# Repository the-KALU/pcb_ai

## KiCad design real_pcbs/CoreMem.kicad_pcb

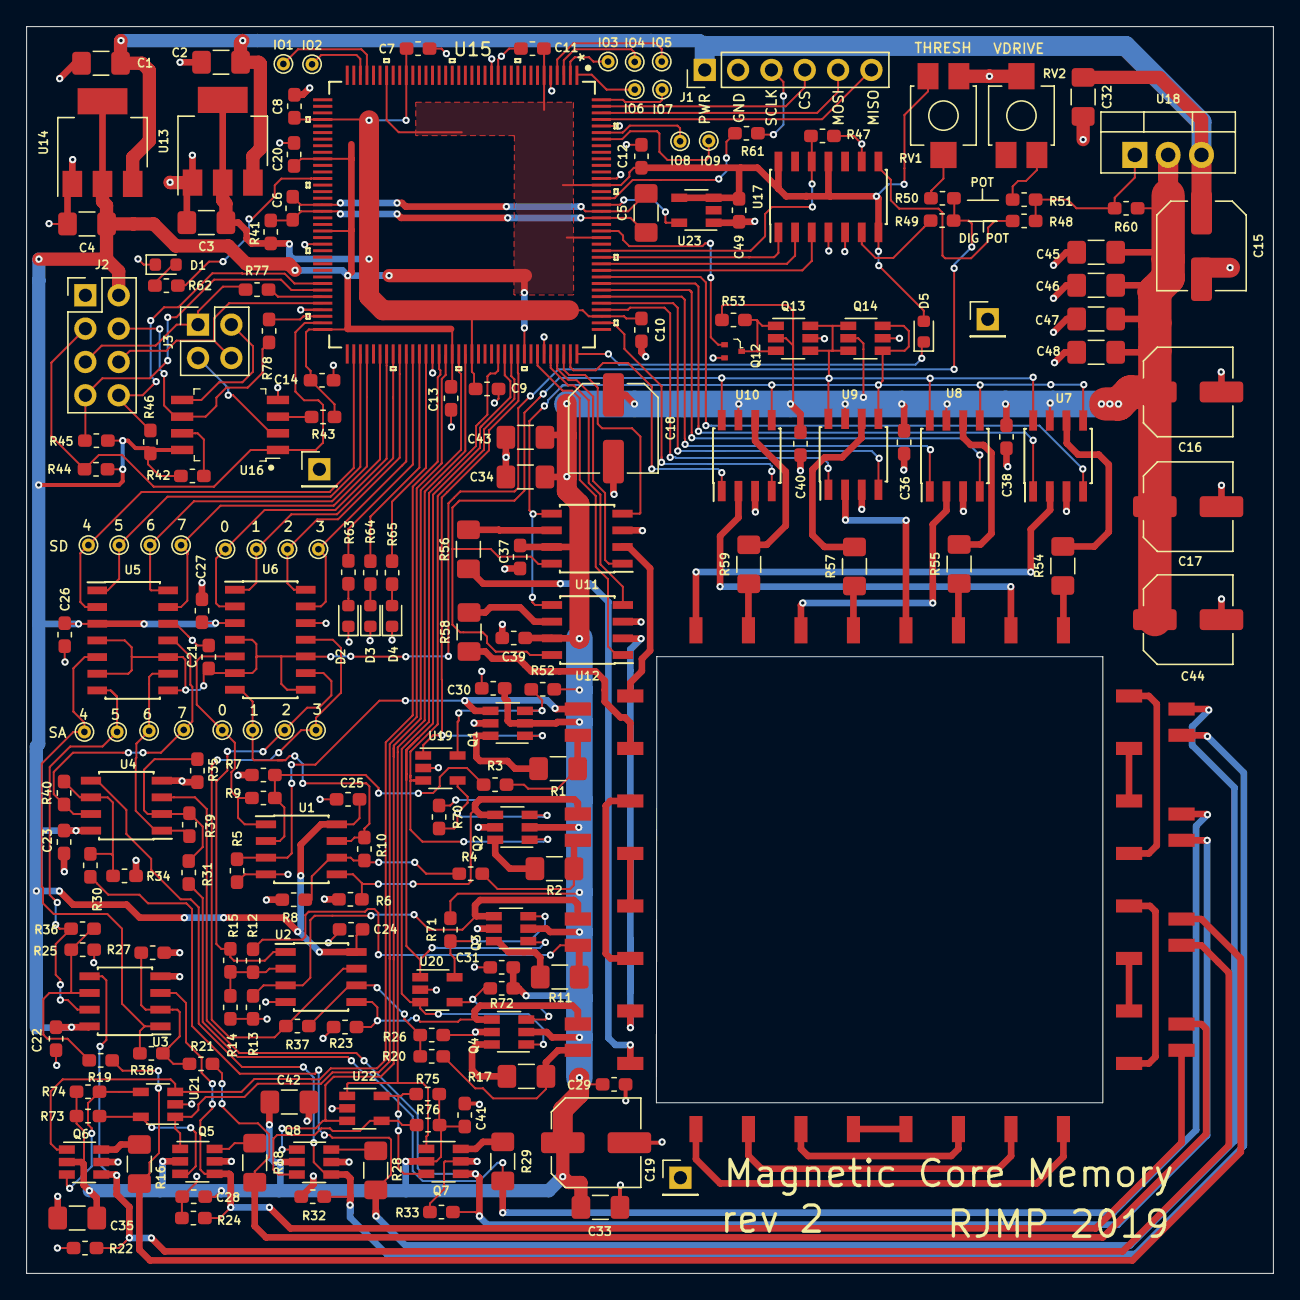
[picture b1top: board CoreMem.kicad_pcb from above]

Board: 2 copper layers, 95.0 x 95.0 mm, 196 parts (0 on the bottom side), 161 nets.

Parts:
C1, C2, C3, C4, C5, C32, C33, C34, C35, C42, C43, C45, C46, C47, C48: 10uF; C_1206_3216Metric_Pad1.42x1.75mm_HandSolder
C6, C7, C8, C9, C10, C11, C12, C13, C14, C20, C21, C22, C23, C24, C25, C26, C27, C28, C29, C30, C31, C36, C37, C38, C39, C40, C41, C49: 0.1uF; C_0603_1608Metric_Pad1.05x0.95mm_HandSolder
C15, C16, C17, C18, C19, C44: 100uF; C_Elec_6.3x7.7
D1, D2, D3, D4: LED; LED_0603_1608Metric
D5: CDBU0520; D_0603_1608Metric
F1: CoreArray
IO1, IO2, IO3, IO4, IO5, IO6, IO7, IO8, IO9: TestPoint; TestPoint_THTPad_D1.0mm_Drill0.5mm
J1: CTRL; PinHeader_1x06_P2.54mm_Vertical
J2: PROG; PinHeader_2x04_P2.54mm_Vertical
J3: Conn_02x02_Odd_Even; PinHeader_2x02_P2.54mm_Vertical
Q1, Q2, Q3, Q4, Q5, Q6, Q7, Q8, Q13, Q14: DMG6602SVTQ-7; TSOT-23-6
Q12: DMG1012T-7; SOT-523
R1, R2, R11, R16, R17, R18, R28, R29, R54, R55, R56, R57, R58, R59: 10; R_1206_3216Metric_Pad1.42x1.75mm_HandSolder
R3, R4, R12, R19, R20, R21, R30, R31: 1k; R_0603_1608Metric_Pad1.05x0.95mm_HandSolder
R5, R6, R7, R8, R9, R10, R13, R14, R15, R22, R23, R24, R25, R26, R27, R32, R33, R34, R35, R36, R37, R38, R39, R40: 22k; R_0603_1608Metric_Pad1.05x0.95mm_HandSolder
R41, R61, R77, R78: 100; R_0603_1608Metric_Pad1.05x0.95mm_HandSolder
R42, R43, R44, R45, R47, R52, R53, R60, R70, R71, R72, R73, R74, R75, R76: 10k; R_0603_1608Metric_Pad1.05x0.95mm_HandSolder
R46: 100k; R_0603_1608Metric_Pad1.05x0.95mm_HandSolder
R48, R49: 0; R_0603_1608Metric_Pad1.05x0.95mm_HandSolder
R50, R51: 0/DNP; R_0603_1608Metric_Pad1.05x0.95mm_HandSolder
R62, R63, R64, R65: 261; R_0603_1608Metric_Pad1.05x0.95mm_HandSolder
RV1, RV2: 10k; ST4EB
TP1: SA0; TestPoint_THTPad_D1.0mm_Drill0.5mm
TP2: SA1; TestPoint_THTPad_D1.0mm_Drill0.5mm
TP3: SA2; TestPoint_THTPad_D1.0mm_Drill0.5mm
TP4: SA4; TestPoint_THTPad_D1.0mm_Drill0.5mm
TP5: SA5; TestPoint_THTPad_D1.0mm_Drill0.5mm
TP6: SA3; TestPoint_THTPad_D1.0mm_Drill0.5mm
TP7: SA6; TestPoint_THTPad_D1.0mm_Drill0.5mm
TP8: SA7; TestPoint_THTPad_D1.0mm_Drill0.5mm
TP9: SD0; TestPoint_THTPad_D1.0mm_Drill0.5mm
TP10: SD1; TestPoint_THTPad_D1.0mm_Drill0.5mm
TP11: SD2; TestPoint_THTPad_D1.0mm_Drill0.5mm
TP12: SD5; TestPoint_THTPad_D1.0mm_Drill0.5mm
TP13: SD4; TestPoint_THTPad_D1.0mm_Drill0.5mm
TP14: SD3; TestPoint_THTPad_D1.0mm_Drill0.5mm
TP15: SD6; TestPoint_THTPad_D1.0mm_Drill0.5mm
TP16: SD7; TestPoint_THTPad_D1.0mm_Drill0.5mm
TP17, TP18, TP19: GND; PinHeader_1x01_P2.54mm_Vertical
U1, U2, U3, U4: OPA2365AIDR; SOIC-8_3.9x4.9mm_P1.27mm
U5, U6: TS864; SOIC-14_3.9x8.7mm_P1.27mm
U7, U8, U9, U10, U11, U12: DMHC3025LSD-13‎; SOIC-8_3.9x4.9mm_P1.27mm
U13: AZ1117-1.2; SOT-223-3_TabPin2
U14: AZ1117-3.3; SOT-223-3_TabPin2
U15: ICE40HX4K-TQ144
U16: W25Q32JVSSIQ_TR; SOIC-8_W5.6mm
U17: MCP42010; SOIC-14_3.9x8.7mm_P1.27mm
U18: LM338; TO-220-3_Vertical
U19, U20, U21, U22: QS5K2; TSOT-23-5
U23: SiT2001B; TSOT-23-5

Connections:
+1V2: C3.1, C7.1, C8.1, C9.1, C10.1, R41.2, U13.2, U15.27, U15.40, U15.92, U15.111
+3V3: C4.1, C11.1, C12.1, C13.1, C14.1, C20.1, C22.1, C23.1, C24.1, C25.1, C26.1, C27.1, C49.1, D5.2, J2.2, R42.2, R43.2, R44.2, R45.2, R46.2, RV1.1, U1.8, U2.8, U3.8, U4.8, U5.3, U6.3, U14.2, U15.6, U15.30, U15.46, U15.57, U15.72, U15.89, U15.100, U15.123, U15.131, U16.8, U17.7, U17.11, U17.14, U23.3, U23.4
/CS: J1.4, U15.143
/DIN: J1.5, U15.142
/DIR: Q12.1, U15.124
/DOUT: J1.6, U15.141
/DRIVE/DIR_F_VD: Q13.4, Q13.6, Q14.1, Q14.3, U7.8, U8.8, U9.8, U10.8, U11.8, U12.8
/DRIVE/DIR_R_VD: Q14.4, Q14.6, U7.5, U8.5, U9.5, U10.5, U11.5, U12.5
/INHIBIT0: Q1.1, U15.99, U19.1
/INHIBIT1: Q2.1, U15.98, U19.3
/INHIBIT2: Q3.1, U15.97, U20.1
/INHIBIT3: Q4.1, U15.96, U20.3
/INHIBIT4: Q5.1, U15.88, U21.1
/INHIBIT5: Q6.1, U15.87, U21.3
/INHIBIT6: Q7.1, U15.91, U22.1
/INHIBIT7: Q8.1, U15.90, U22.3
/POT_CS: U15.120, U17.1
/POT_MOSI: U15.118, U17.3
/POT_SCK: U15.119, U17.2
/POT_SHDN: R47.1, U15.121, U17.12
/S0_N: F1.34, R1.2, R3.2
/S0_P: F1.33, Q1.4, R5.2, U1.3
/S1_N: F1.36, R2.2, R4.2
/S1_P: F1.35, Q2.4, R6.2, U1.5
/S2_N: F1.38, R11.2, R12.2
/S2_P: F1.37, Q3.4, R13.2, U2.3
/S3_N: F1.40, R17.2, R20.2
/S3_P: F1.39, Q4.4, R23.2, U2.5
/S4_N: F1.47, R18.2, R21.2
/S4_P: F1.48, Q5.4, R24.2, U3.3
/S5_N: F1.45, R16.2, R19.2
/S5_P: F1.46, Q6.4, R22.2, U3.5
/S6_N: F1.43, R29.2, R31.2
/S6_P: F1.44, Q7.4, R33.2, U4.3
/S7_N: F1.41, R28.2, R30.2
/S7_P: F1.42, Q8.4, R32.2, U4.5
/SCLK: J1.3, R61.2
/SCLK_F: R61.1, U15.129
/SD0: TP9.1, U6.2, U15.79
/SD1: TP10.1, U6.1, U15.80
/SD2: TP11.1, U6.14, U15.81
/SD3: TP14.1, U6.13, U15.82
/SD4: TP13.1, U5.2, U15.74
/SD5: TP12.1, U5.1, U15.75
/SD6: TP15.1, U5.14, U15.76
/SD7: TP16.1, U5.13, U15.78
/SENSE_Conditioning/INHIBIT0n: Q1.3, R52.1, U19.5
/SENSE_Conditioning/INHIBIT1n: Q2.3, R70.2, U19.4
/SENSE_Conditioning/INHIBIT2n: Q3.3, R71.1, U20.5
/SENSE_Conditioning/INHIBIT3n: Q4.3, R72.2, U20.4
/SENSE_Conditioning/INHIBIT4n: Q5.3, R73.1, U21.5
/SENSE_Conditioning/INHIBIT5n: Q6.3, R74.1, U21.4
/SENSE_Conditioning/INHIBIT6n: Q7.3, R75.1, U22.5
/SENSE_Conditioning/INHIBIT7n: Q8.3, R76.1, U22.4
/SENSE_Conditioning/SA0: R9.2, TP1.1, U1.1, U6.5
/SENSE_Conditioning/SA1: R10.2, TP2.1, U1.7, U6.7
/SENSE_Conditioning/SA2: R15.2, TP3.1, U2.1, U6.9
/SENSE_Conditioning/SA3: R37.2, TP6.1, U2.7, U6.11
/SENSE_Conditioning/SA4: R38.2, TP4.1, U3.1, U5.5
/SENSE_Conditioning/SA5: R36.2, TP5.1, U3.7, U5.7
/SENSE_Conditioning/SA6: R39.2, TP7.1, U4.1, U5.9
/SENSE_Conditioning/SA7: R40.2, TP8.1, U4.7, U5.11
/SENSE_THRESH: C21.1, R49.1, R50.1, U5.4, U5.6, U5.8, U5.10, U6.4, U6.6, U6.8, U6.10
/VDRIVE_CONTROL: R48.1, R51.2, R60.2, U18.1
/X0_EN_F: U11.4, U15.106
/X0_EN_R: U11.1, U15.105
/X0_N: F1.8, R56.1
/X0_P: F1.1, U11.2
/X1_EN_F: U12.4, U15.104
/X1_EN_R: U12.1, U15.102
/X1_N: F1.2, R58.1
/X1_P: F1.7, U12.2
/Y0_EN_F: U7.4, U15.117
/Y0_EN_R: U7.1, U15.116
/Y0_N: F1.31, R59.1
/Y0_P: F1.32, U7.2
/Y1_EN_F: U8.4, U15.115
/Y1_EN_R: U8.1, U15.114
/Y1_N: F1.29, R57.1
/Y1_P: F1.30, U8.2
/Y2_EN_F: U9.4, U15.113
/Y2_EN_R: U9.1, U15.112
/Y2_N: F1.27, R55.1
/Y2_P: F1.28, U9.2
/Y3_EN_F: U10.4, U15.110
/Y3_EN_R: U10.1, U15.107
/Y3_N: F1.25, R54.1
/Y3_P: F1.26, U10.2
/controller/CDONE: J2.8, R46.1, U15.65
/controller/CLKIN: U15.128, U23.5
/controller/CRESET_B: J2.7, R45.1, U15.66
/controller/FLASH_DI: J3.2, U16.5
/controller/FLASH_DO: J3.3, U16.2
/controller/GNDPLL: C5.2, C6.2, U15.53, U15.127
/controller/LED0: R62.1, U15.49
/controller/LED1: R63.1, U15.83
/controller/LED2: R64.1, U15.84
/controller/LED3: R65.1, U15.85
/controller/SPI_SCK: J2.4, R78.1, U16.6
/controller/SPI_SDI: J2.6, J3.4, U15.68
/controller/SPI_SDO: J2.5, J3.1, R77.1
/controller/SPI_SS: J2.3, R44.1, U15.71, U16.1
/controller/VCCPLL: C5.1, C6.1, R41.1, U15.54, U15.126
GND: C1.2, C2.2, C3.2, C4.2, C7.2, C8.2, C9.2, C10.2, C11.2, C12.2, C13.2, C14.2, C15.2, C16.2, C17.2, C18.2, C19.2, C20.2, C21.2, C22.2, C23.2, C24.2, C25.2, C26.2, C27.2, C28.2, C29.2, C30.2, C31.2, C32.2, C33.2, C34.2, C35.2, C36.2, C37.2, C38.2, C39.2, C40.2, C41.2, C42.2, C43.2, C44.2, C45.2, C46.2, C47.2, C48.2, C49.2, D1.1, D2.1, D3.1, D4.1, J1.2, J2.1, Q1.5, Q2.5, Q3.5, Q4.5, Q5.5, Q6.5, Q7.5, Q8.5, Q12.2, Q13.5, Q14.5, R5.1, R6.1, R7.1, R8.1, R13.1, R14.1, R22.1, R23.1, R24.1, R25.1, R26.1, R27.1, R32.1, R33.1, R34.1, R35.1, R47.2, RV1.3, RV2.2, TP17.1, TP18.1, TP19.1, U1.4, U2.4, U3.4, U4.4, U5.12, U6.12, U7.3, U8.3, U9.3, U10.3, U11.3, U12.3, U13.1, U14.1, U15.5, U15.13, U15.14, U15.59, U15.69, U15.86, U15.103, U15.132, U15.140, U16.4, U17.4, U17.5, U17.9, U19.2, U20.2, U21.2, U22.2, U23.1
unnamed: D1.2, R62.2
unnamed: D2.2, R63.2
unnamed: D3.2, R64.2
unnamed: D4.2, R65.2
unnamed: D5.1, U15.108
unnamed: F1.3, F1.6
unnamed: F1.4, F1.5
unnamed: F1.10, F1.15
unnamed: F1.11, F1.14
unnamed: F1.12, F1.13
unnamed: F1.9, F1.16
unnamed: F1.17, F1.20
unnamed: F1.18, F1.19
unnamed: F1.21, F1.24
unnamed: F1.22, F1.23
unnamed: IO1.1, U15.33
unnamed: IO2.1, U15.34
unnamed: IO3.1, U15.2
unnamed: IO4.1, U15.3
unnamed: IO5.1, U15.4
unnamed: IO6.1, U15.1
unnamed: IO7.1, U15.144
unnamed: IO8.1, U15.139
unnamed: IO9.1, U15.138
unnamed: Q1.6, R1.1
unnamed: Q2.6, R2.1
unnamed: Q3.6, R11.1
unnamed: Q4.6, R17.1
unnamed: Q5.6, R18.1
unnamed: Q6.6, R16.1
unnamed: Q7.6, R29.1
unnamed: Q8.6, R28.1
unnamed: Q12.3, Q13.1, Q13.3, R53.2
unnamed: R3.1, R7.2, R9.1, U1.2
unnamed: R4.1, R8.2, R10.1, U1.6
unnamed: R12.1, R14.2, R15.1, U2.2
unnamed: R19.1, R25.2, R36.1, U3.6
unnamed: R20.1, R26.2, R37.1, U2.6
unnamed: R21.1, R27.2, R38.1, U3.2
unnamed: R30.1, R34.2, R40.1, U4.6
unnamed: R31.1, R35.2, R39.1, U4.2
unnamed: R42.1, U16.7
unnamed: R43.1, U16.3
unnamed: R48.2, U17.8
unnamed: R49.2, U17.6
unnamed: R50.2, RV1.2
unnamed: R51.1, RV2.1
unnamed: R54.2, U7.6
unnamed: R55.2, U8.6
unnamed: R56.2, U11.6
unnamed: R57.2, U9.6
unnamed: R58.2, U12.6
unnamed: R59.2, U10.6
unnamed: R77.2, U15.67
unnamed: R78.2, U15.70
VBUS: C1.1, C2.1, C15.1, C32.1, J1.1, U13.3, U14.3, U18.3
Vdrive: C16.1, C17.1, C18.1, C19.1, C28.1, C29.1, C30.1, C31.1, C33.1, C34.1, C35.1, C36.1, C37.1, C38.1, C39.1, C40.1, C41.1, C42.1, C43.1, C44.1, C45.1, C46.1, C47.1, C48.1, Q1.2, Q2.2, Q3.2, Q4.2, Q5.2, Q6.2, Q7.2, Q8.2, Q13.2, Q14.2, R52.2, R53.1, R60.1, R70.1, R71.2, R72.1, R73.2, R74.2, R75.2, R76.2, U7.7, U8.7, U9.7, U10.7, U11.7, U12.7, U18.2

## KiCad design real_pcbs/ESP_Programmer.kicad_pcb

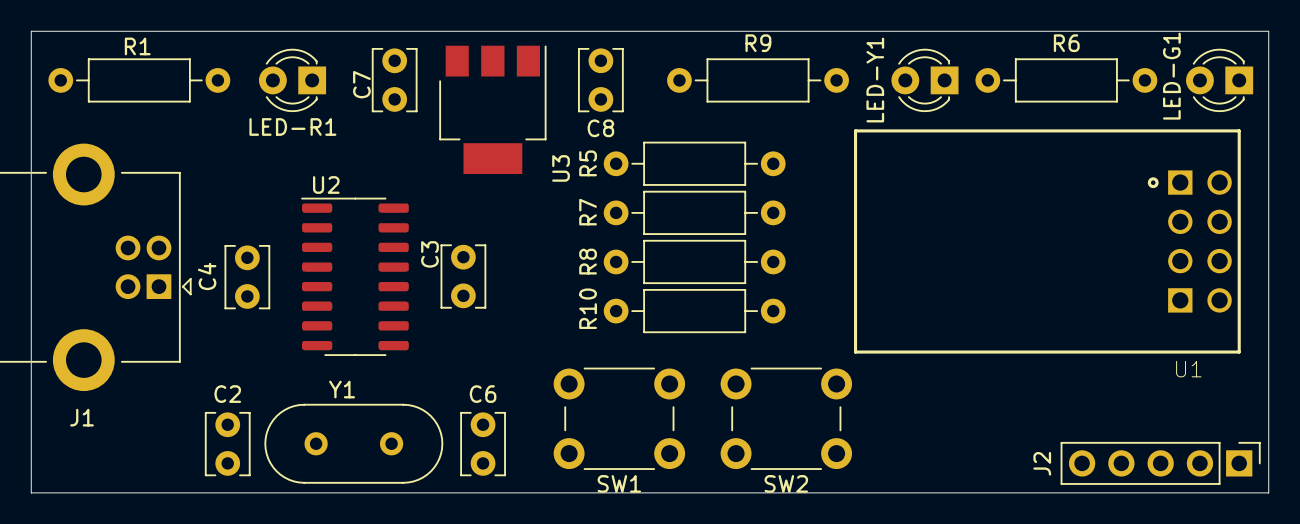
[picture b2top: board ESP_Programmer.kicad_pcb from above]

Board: 2 copper layers, 80.0 x 29.8 mm, 24 parts (0 on the bottom side), 17 nets, no tracks yet.

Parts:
C2, C6: 22pf; C_Disc_D3.8mm_W2.6mm_P2.50mm
C3: 105; C_Disc_D3.8mm_W2.6mm_P2.50mm
C4, C8: 104; C_Disc_D3.8mm_W2.6mm_P2.50mm
C7: 106; C_Disc_D3.8mm_W2.6mm_P2.50mm
J1: USB_B; USB_B_Lumberg_2411_02_Horizontal
J2: Conn_01x05_Male; PinHeader_1x05_P2.54mm_Vertical
LED-G1: LED; LED_D3.0mm_Clear
LED-R1: LED; LED_D3.0mm_Clear
LED-Y1: LED; LED_D3.0mm_Clear
R1, R6, R9: 330; R_Axial_DIN0207_L6.3mm_D2.5mm_P10.16mm_Horizontal
R5, R7, R8, R10: 10K; R_Axial_DIN0207_L6.3mm_D2.5mm_P10.16mm_Horizontal
SW1: FLASH; SW_PUSH_6mm_H4.3mm
SW2: RESET; SW_PUSH_6mm_H4.3mm
U1: ESP8266-01_ESP-01; ESP-01
U2: CH340G; SOIC-16_3.9x9.9mm_P1.27mm
U3: AMS1117; SOT-223-3_TabPin2
Y1: 12MHz; Crystal_HC49-4H_Vertical

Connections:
3.3v: C8.1, J2.3, R5.2, R7.1, R8.1, R9.1, U1.8, U3.2
+5V: C3.1, C7.1, J1.1, J2.2, R1.1, U2.16, U3.3
/CH_PD: R8.2, U1.6
/D+: J1.3, U2.5
/D-: J1.2, U2.6
/IO0: R5.1, SW1.2, U1.2
/IO2: R6.1, U1.3
/RST: R7.2, SW2.2, U1.7
ESP_RXD: J2.4, U1.1, U2.2
ESP_TXD: J2.5, R10.1, U1.5, U2.3
GND: C2.2, C3.2, C4.2, C6.2, C7.2, C8.2, J1.4, J1.5, J2.1, LED-G1.1, LED-R1.1, LED-Y1.1, R10.2, SW1.1, SW2.1, U1.4, U2.1, U3.1
unnamed: C2.1, U2.7, Y1.1
unnamed: C4.1, U2.4
unnamed: C6.1, U2.8, Y1.2
unnamed: LED-G1.2, R6.2
unnamed: LED-R1.2, R1.2
unnamed: LED-Y1.2, R9.2

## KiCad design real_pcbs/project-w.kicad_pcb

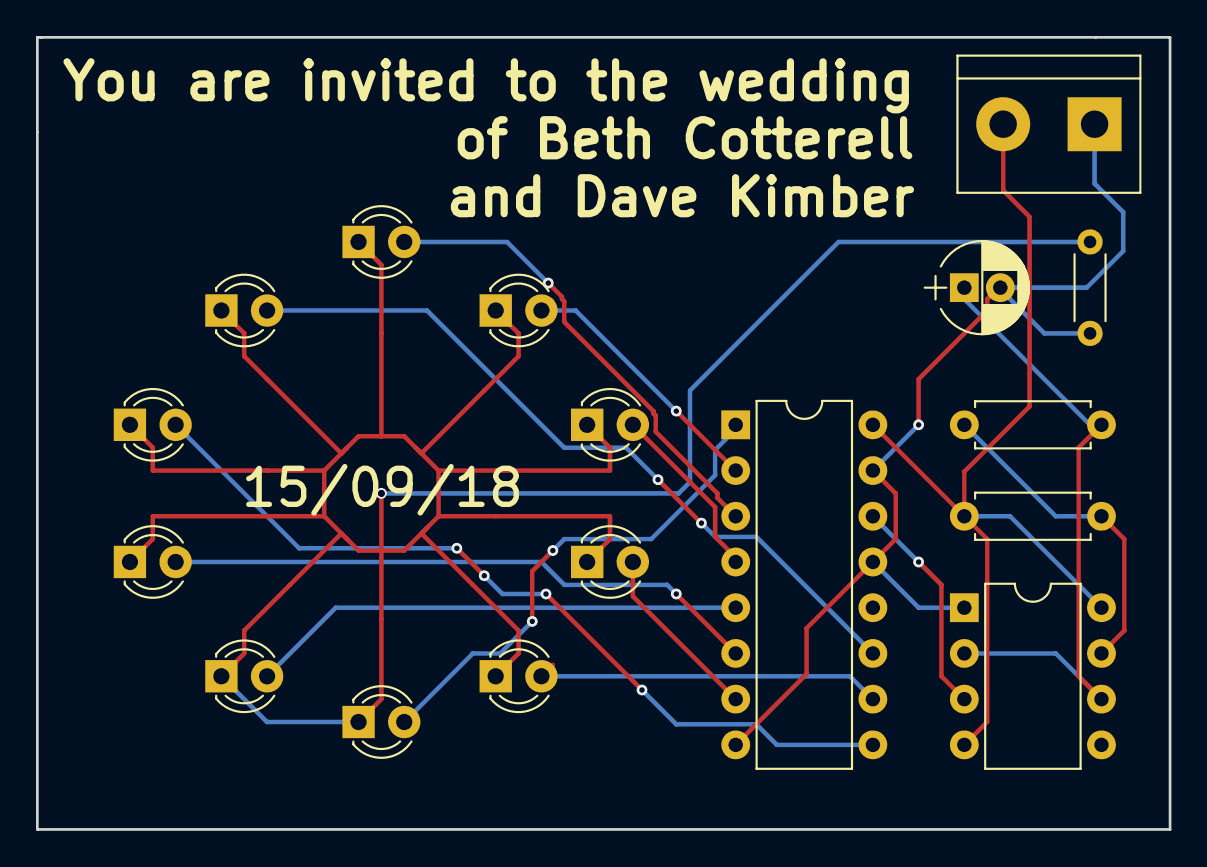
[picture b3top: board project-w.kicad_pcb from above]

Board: 2 copper layers, 62.9 x 44.0 mm, 17 parts (0 on the bottom side), 16 nets.

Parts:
C1: 1uF; CP_Radial_D5.0mm_P2.00mm
D1, D2, D3, D4, D5, D6, D7, D8, D9, D10: LED; LED_D3.0mm
J1: Screw_Terminal_01x02; TerminalBlock_bornier-2_P5.08mm
R1: 47K; R_Axial_DIN0207_L6.3mm_D2.5mm_P7.62mm_Horizontal
R2: 1K; R_Axial_DIN0207_L6.3mm_D2.5mm_P7.62mm_Horizontal
R3: 1K; R_Axial_DIN0204_L3.6mm_D1.6mm_P5.08mm_Horizontal
U1: NE555; DIP-8_W7.62mm
U2: CD4017; DIP-16_W7.62mm

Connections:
unnamed: C1.1, R1.2, U1.2, U1.6
unnamed: D1.1, D2.1, D3.1, D4.1, D5.1, D6.1, D7.1, D8.1, D9.1, D10.1, R3.1
unnamed: D1.2, U2.3
unnamed: D2.2, U2.2
unnamed: D3.2, U2.4
unnamed: D4.2, U2.7
unnamed: D5.2, U2.10
unnamed: D6.2, U2.1
unnamed: D7.2, U2.5
unnamed: D8.2, U2.6
unnamed: D9.2, U2.9
unnamed: D10.2, U2.11
unnamed: R1.1, R2.2, U1.7
unnamed: U1.3, U2.14
VDD: J1.2, R2.1, U1.4, U1.8, U2.16
VSS: C1.2, J1.1, R3.2, U1.1, U2.8, U2.13, U2.15

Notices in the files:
parts and their libraries:
Copyright 2016 Accelerated Designs. All rights reserved.
